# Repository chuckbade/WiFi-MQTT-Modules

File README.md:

Chuck Bade's Guide to using MQTT on ESP8266-Based Modules with JMRI for Model Trains

Update: All the sketches have been updated to be OTA-compatible (Over The Air programming). 
This will allow you to make updates without connecting the USB cable to the module.  The
first time you load one of these sketches however, you will have to use the cable and select the COM port, but after that you will be able to select the network port that's shown on the serial monitor on startup.  If you're using a WiFi connection on your PC, make sure the connection is set for Private not Public.

This is an inexpensive system of hardware and software for running model train accessories with JMRI.  I'm using a DCC++ setup for a base station, but any base station should be able to be used, as long as JMRI will allow the MQTT protocol to exist along side the other protocol.  Each module has a ESP8266-based Wemos D1 Mini (or compatible) that sends and receives messages to and from JMRI.  These messages are sent via the MQTT protocol, which makes programming very straightforward using the Arduino IDE.  JMRI is setup to use both the MQTT and DCC++ protocols.

Note this uses both the DCC++ connection from JMRI, and the MQTT connection.  Each module connects to the MQTT broker and uses specific topics and messages to communicate with JMRI.  Outputs are prefixed with MT and inputs are prefixed with MS.

To build a system, you will need some knowledge of electronics and software, but only at a hobbyist's level.  Before taking this on, I would recommend buying a D1 Mini and programming it to flash the on-board LED, then hook up an external LED and make it flash.  If you get that working, you've done the hard part, getting Arduino IDE set up.

I currently have 8 circuit boards designed for use with JMRI/MQTT.  
- BC Shield - Used for feed the DCC signal to block controllers using standard CAT5 cables.
- Block Controller - Tested and in use on my layout.
- Turnout Controller - Tested and in use on my layout.
- Turntable Controller - Nearly ready, still has a bug.
- 5 Ray Sensor - For 5 rays of a staging yard or turntable.
- Bridge Detector - For connecting two optical sensors under a turntable bridge.
- MQTT Monitor - A useful LCD-based monitoring tool that can send messages.
- Robocut - For running a servo inside a boxcar to uncouple other cars from it.
- 
I may sell blank boards or just provide the files to have your own made.  I haven't decided which way to go with that.

I am a retired software engineer, and I have been involved in electronics since my dad bought some CK722 transistors and a book from Berstein Applebee, from which we built various circuits. Now I design my own hardware and write the software to run it.  I was trained in electronics (PMEL) in the Marine Corps and since I never had a formal education in electrical engineering, my designs are based on what I've learned along the way and are a product of much trial and some error. I have a Bachelor's Degree in Computer Science.

I had tried to use S88N to monitor sensors around the layout, but found it to be prone to electrical noise, so S88 is gone, but I've repurposed the CAT5 cables to route the DCC signal and power to the block controllers.  There's too much voltage drop to maintain an adequate level from the five volt supply, so some extra voltage taps are required at the far ends of the the layout.  My train room is 15' by 15' with track on all four walls.

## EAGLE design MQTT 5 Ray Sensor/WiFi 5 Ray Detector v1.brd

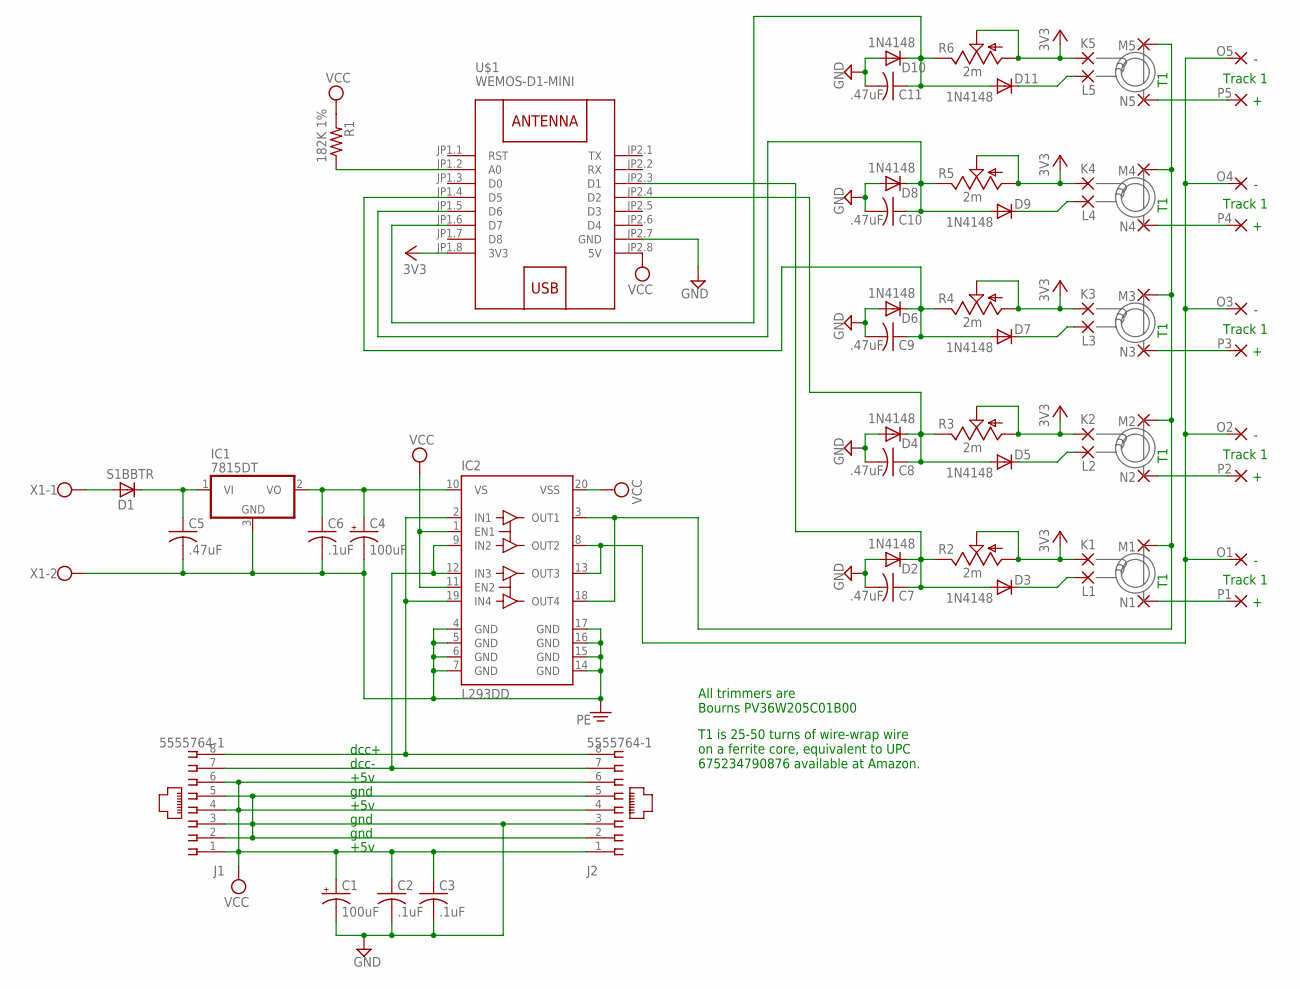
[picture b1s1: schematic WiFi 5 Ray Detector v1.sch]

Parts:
C1, C4: 100uF; E3,5-8
C2, C3, C6: .1uF; C1206
C5, C7, C8, C9, C10, C11: .47uF; C1206
D1: S1BBTR; DO-214AC
D2, D3, D4, D5, D6, D7, D8, D9, D10, D11: 1N4148; SOD123
IC1: 7815DT; TO252
IC2: L293DD; SO20
J1, J2: 5555764-1; 520426-4
K1, K2, K3, K4, K5: 2,15/1,0
L1, L2, L3, L4, L5: 2,15/1,0
M1, M2, M3, M4, M5: NA; 2,15/1,0
N1, N2, N3, N4, N5: NA; 2,15/1,0
O1, O2, O3, O4, O5: NA; 2,15/1,0
P1, P2, P3, P4, P5: NA; 2,15/1,0
R1: 182K 1%; M1206
R2, R3, R4, R5, R6: 2m; S63P
U$1: WEMOS-D1-MINI
X1: W237-102

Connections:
3V3: K1.1, K2.1, K3.1, K4.1, K5.1, R2.A, R2.S, R3.A, R3.S, R4.A, R4.S, R5.A, R5.S, R6.A, R6.S, U$1.JP1.8 (3V3)
GND: C1.-, C2.2, C3.2, C7.2, C8.2, C9.2, C10.2, C11.2, D2.A, D4.A, D6.A, D8.A, D10.A, J1.2, J1.3, J1.5, J2.2, J2.3, J2.5, U$1.JP2.7 (GND)
J1: N1.1, P1.1
J2: N2.1, P2.1
J3: N3.1, P3.1
J4: N4.1, P4.1
J5: N5.1, P5.1
unnamed: D5.C, L2.1
unnamed: C9.1, D6.C, D7.A, R4.E, U$1.JP1.4 (D5)
unnamed: C7.1, D2.C, D3.A, R2.E, U$1.JP2.3 (D1)
unnamed: D1.A, X1.1
unnamed: C5.1, D1.C, IC1.1 (VI)
unnamed: C8.1, D4.C, D5.A, R3.E, U$1.JP2.4 (D2)
unnamed: IC2.9 (IN2), IC2.12 (IN3), J1.7, J2.7
unnamed: D7.C, L3.1
unnamed: C10.1, D8.C, D9.A, R5.E, U$1.JP1.5 (D6)
unnamed: D9.C, L4.1
unnamed: C11.1, D10.C, D11.A, R6.E, U$1.JP1.6 (D7)
unnamed: R1.1, U$1.JP1.2 (A0)
unnamed: D11.C, L5.1
unnamed: IC2.2 (IN1), IC2.19 (IN4), J1.8, J2.8
unnamed: D3.C, L1.1
OUT+: IC2.3 (OUT1), IC2.18 (OUT4), M1.1, M2.1, M3.1, M4.1, M5.1
OUT-: IC2.8 (OUT2), IC2.13 (OUT3), O1.1, O2.1, O3.1, O4.1, O5.1
PE: C4.-, C5.2, C6.2, IC1.3 (GND), IC2.4 (GND), IC2.5 (GND), IC2.6 (GND), IC2.7 (GND), IC2.14 (GND), IC2.15 (GND), IC2.16 (GND), IC2.17 (GND), X1.2
VCC: C1.+, C2.1, C3.1, IC2.1 (EN1), IC2.11 (EN2), IC2.20 (VSS), J1.1, J1.4, J1.6, J2.1, J2.4, J2.6, R1.2, U$1.JP2.8 (5V)
VS: C4.+, C6.1, IC1.2 (VO), IC2.10 (VS)

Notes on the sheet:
gnd
+5v
dcc+
dcc-
T1 is 25-50 turns of wire-wrap wire on a ferrite core, equivalent to UPC 675234790876 available at Amazon.
All trimmers are Bourns‎ PV36W205C01B00
Track 1

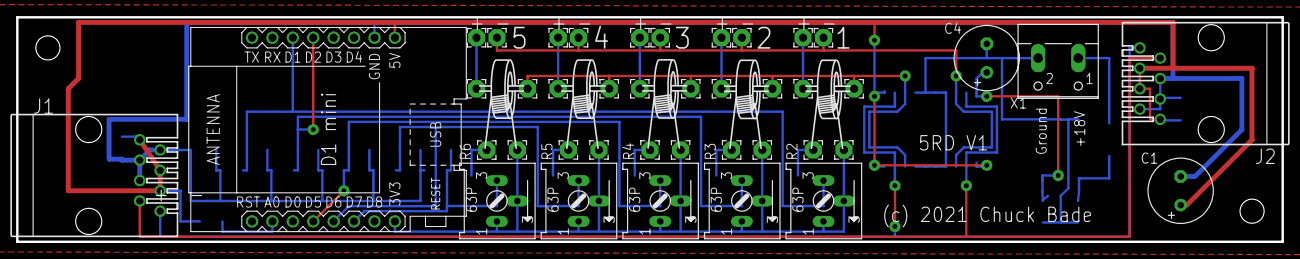
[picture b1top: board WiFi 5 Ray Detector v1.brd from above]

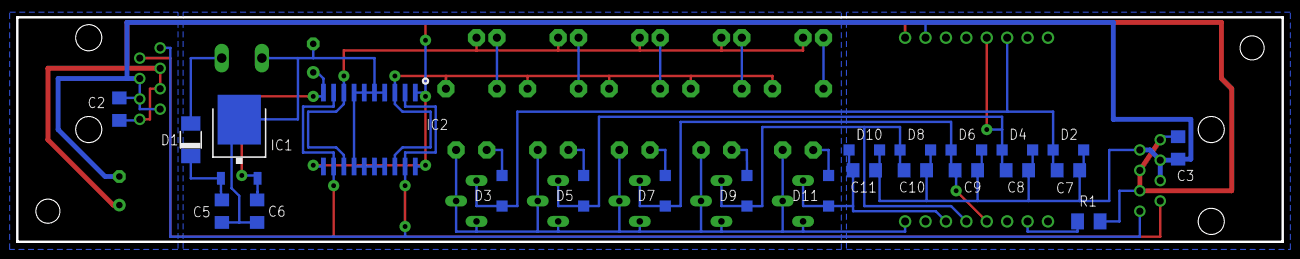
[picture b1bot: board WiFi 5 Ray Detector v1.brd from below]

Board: 2 copper layers, 157.5 x 27.9 mm, 66 parts (23 on the bottom side), 27 nets.

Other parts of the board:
U$3, U$4: 4-40SCREW

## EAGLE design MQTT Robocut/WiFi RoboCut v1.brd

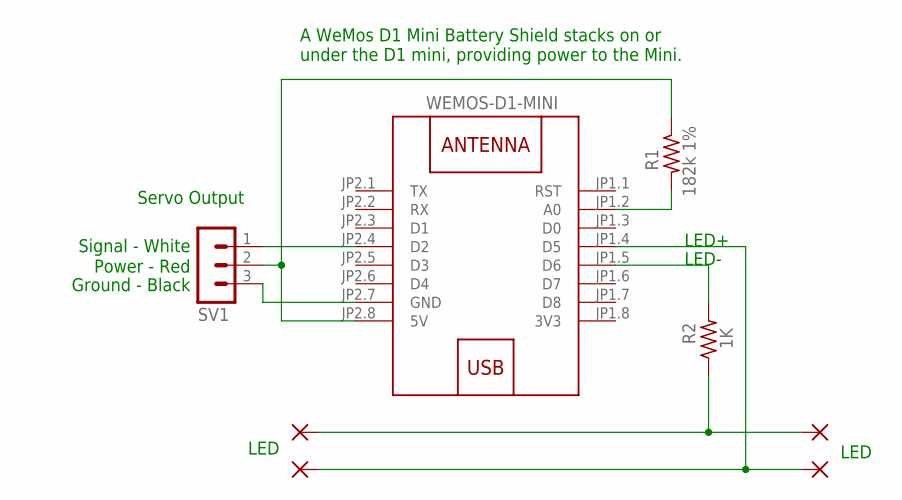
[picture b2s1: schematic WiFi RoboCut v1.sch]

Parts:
PAD1, PAD2, PAD3, PAD4: 2,15/1,0
R1: 182k 1%; R1206
R2: 1K; R1206
SV1: MA03-1
U$1: WEMOS-D1-MINI

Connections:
3V3: U$1.JP1.8 (3V3)
GND: SV1.3, U$1.JP2.7 (GND)
unnamed: R1.2, U$1.JP1.2 (A0)
unnamed: SV1.1, U$1.JP2.4 (D2)
unnamed: PAD1.1, PAD3.1, R2.1
unnamed: PAD2.1, PAD4.1, U$1.JP1.4 (D5)
unnamed: R2.2, U$1.JP1.5 (D6)
VCC: R1.1, SV1.2, U$1.JP2.8 (5V)

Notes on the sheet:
LED+
LED-
Signal - White
Power - Red
Ground - Black
Servo Output
LED
A WeMos D1 Mini Battery Shield stacks on or under the D1 mini, providing power to the Mini.

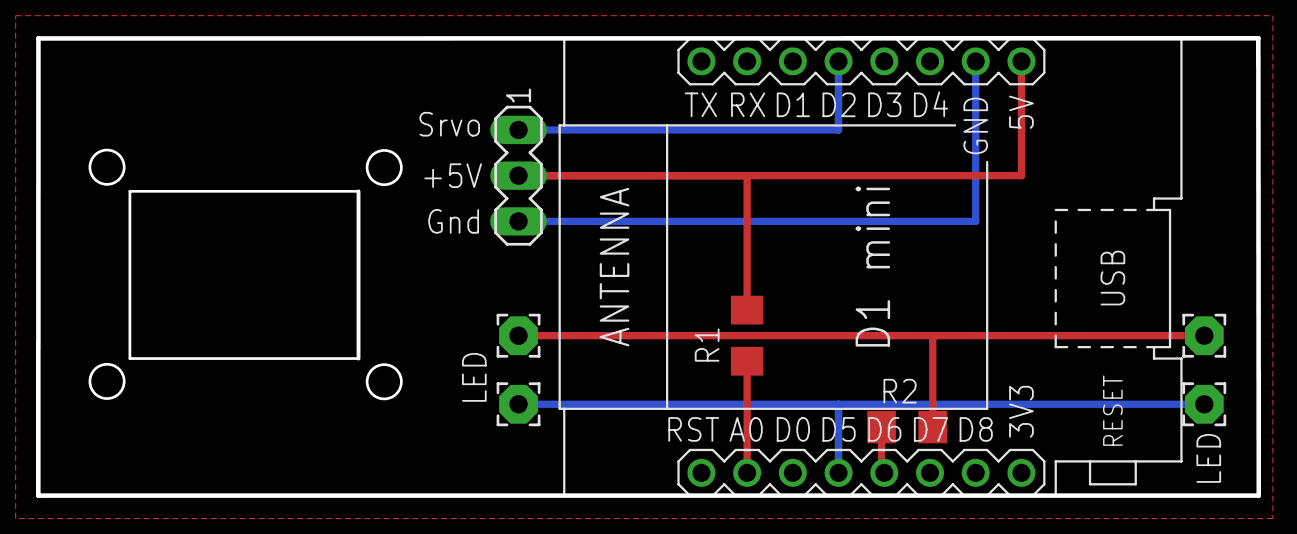
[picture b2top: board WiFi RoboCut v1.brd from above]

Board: 2 copper layers, 67.8 x 25.4 mm, 8 parts (0 on the bottom side), 7 nets.

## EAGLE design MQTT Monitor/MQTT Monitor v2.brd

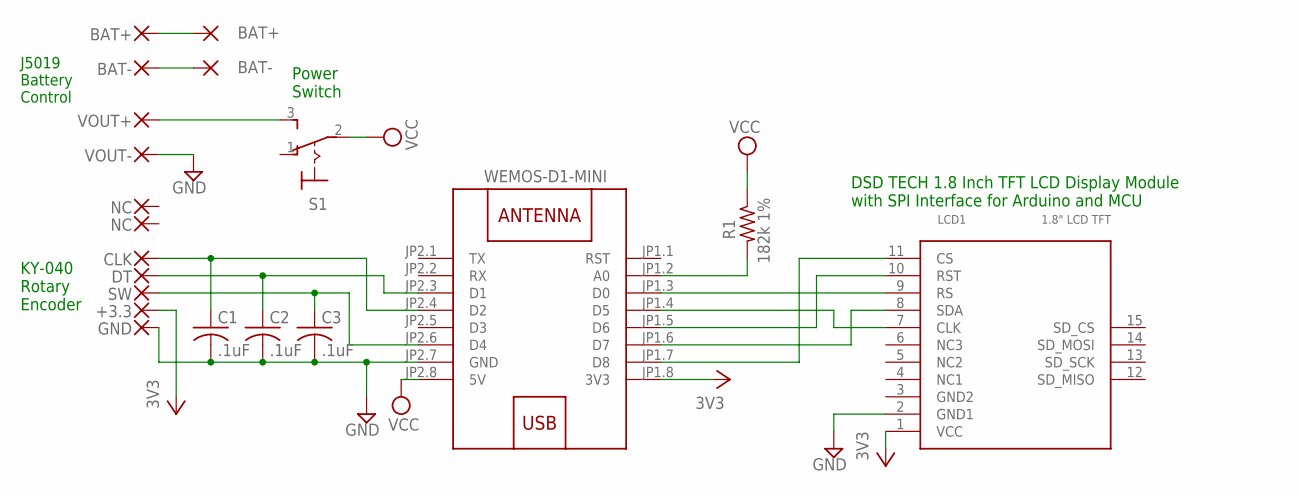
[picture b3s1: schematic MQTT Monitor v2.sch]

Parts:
C1, C2, C3: .1uF; C1206
LCD1: 1.8" LCD TFT; DSDTECH1.8"TFT
PAD1: CLK; 2,15/1,0
PAD2: DT; 2,15/1,0
PAD3: SW; 2,15/1,0
PAD4: +3.3; 2,15/1,0
PAD5: GND; 2,15/1,0
PAD6: VOUT+; 2,15/1,0
PAD7: VOUT-; 2,15/1,0
PAD8, PAD10: BAT+; 2,15/1,0
PAD9, PAD11: BAT-; 2,15/1,0
PAD12, PAD13: NC; 2,15/1,0
R1: 182k 1%; R1206
S1: 320-916
U$1: WEMOS-D1-MINI

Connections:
3V3: LCD1.1 (VCC), PAD4.1, U$1.JP1.8 (3V3)
5V: R1.1, S1.2, U$1.JP2.8 (5V)
GND: C1.2, C2.2, C3.2, LCD1.2 (GND1), PAD5.1, PAD7.1, U$1.JP2.7 (GND)
unnamed: R1.2, U$1.JP1.2 (A0)
unnamed: C3.1, PAD3.1, U$1.JP2.6 (D4)
unnamed: LCD1.7 (CLK), U$1.JP1.4 (D5)
unnamed: LCD1.8 (SDA), U$1.JP1.6 (D7)
unnamed: LCD1.9 (RS), U$1.JP1.3 (D0)
unnamed: LCD1.10 (RST), U$1.JP1.5 (D6)
unnamed: LCD1.11 (CS), U$1.JP1.7 (D8)
unnamed: PAD8.1, PAD10.1
unnamed: PAD9.1, PAD11.1
unnamed: C2.1, PAD2.1, U$1.JP2.3 (D1)
unnamed: C1.1, PAD1.1, U$1.JP2.4 (D2)
unnamed: PAD6.1, S1.3 (S)

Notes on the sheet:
KY-040 Rotary Encoder
J5019 Battery Control
Power Switch
DSD TECH 1.8 Inch TFT LCD Display Module with SPI Interface for Arduino and MCU

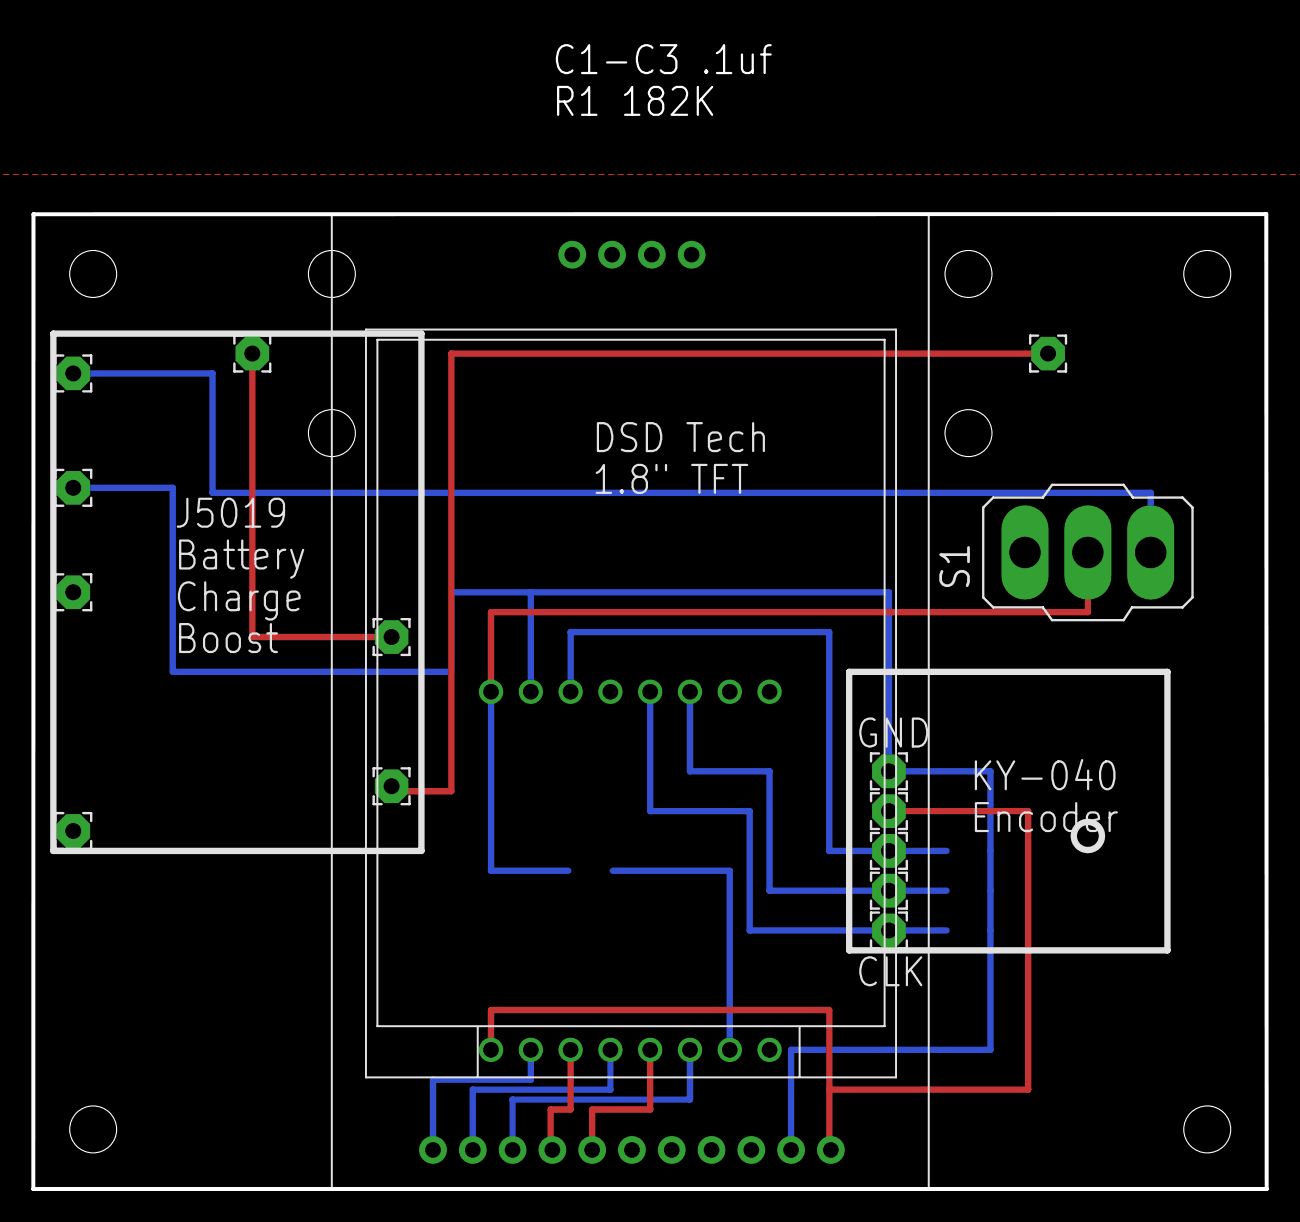
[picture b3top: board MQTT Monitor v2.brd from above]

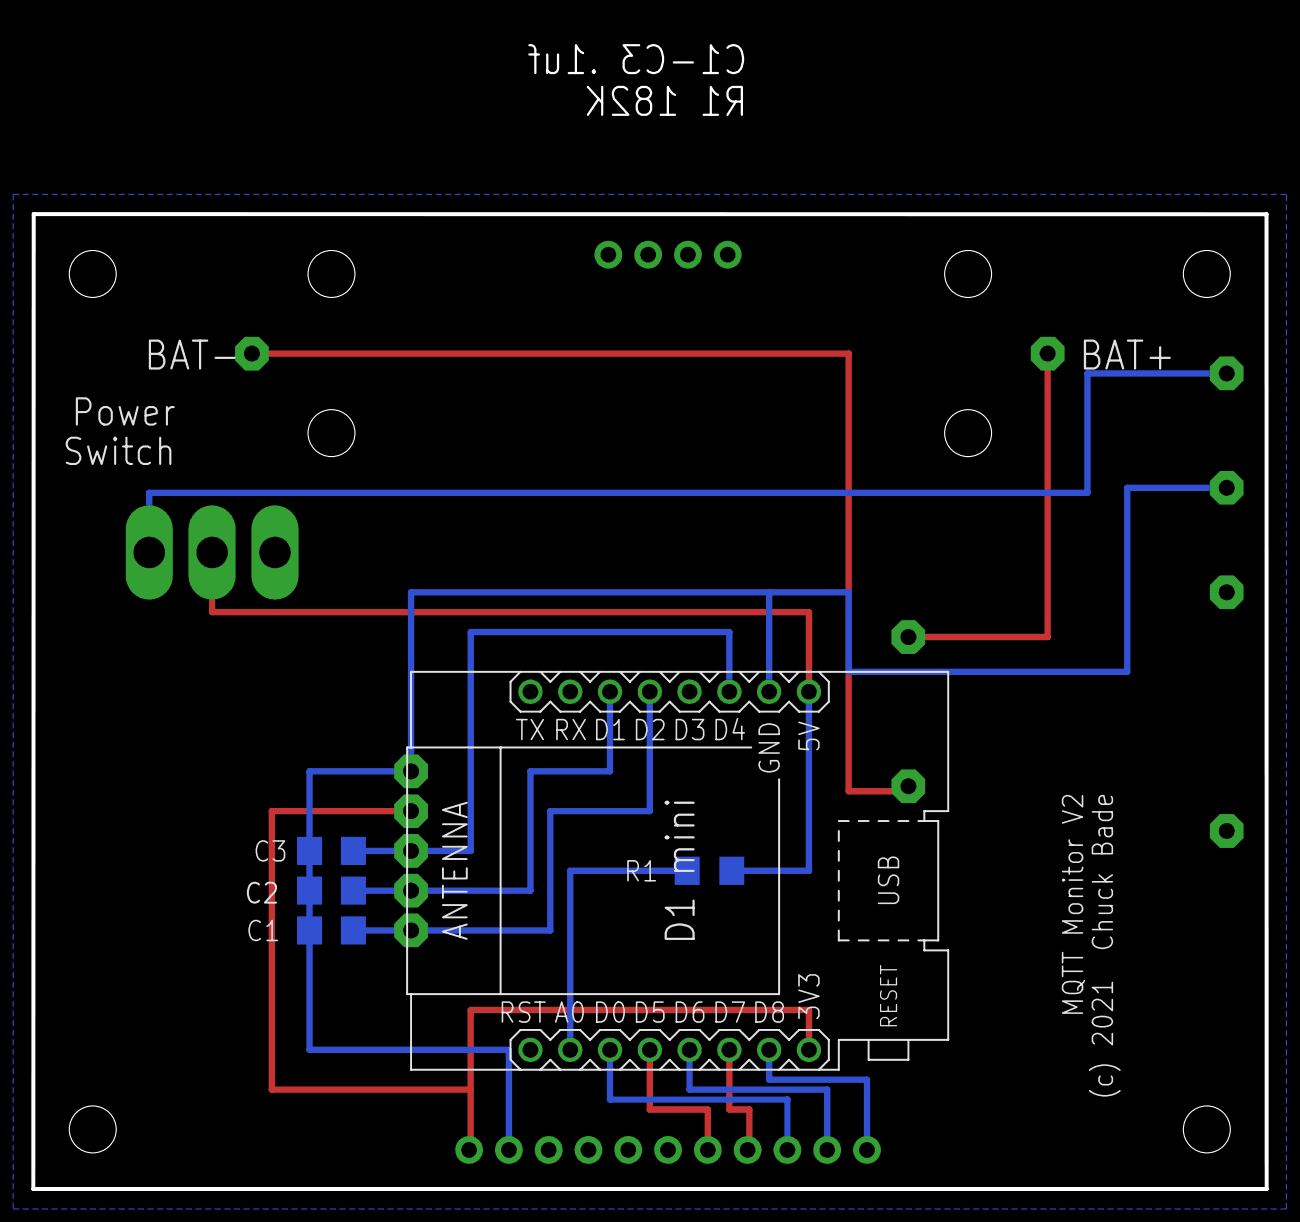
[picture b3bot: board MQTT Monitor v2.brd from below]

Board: 2 copper layers, 78.7 x 73.8 mm, 28 parts (13 on the bottom side), 15 nets.

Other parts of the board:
U$3, U$4, U$5, U$6, U$7, U$8, U$9, U$10: 4-40SCREW

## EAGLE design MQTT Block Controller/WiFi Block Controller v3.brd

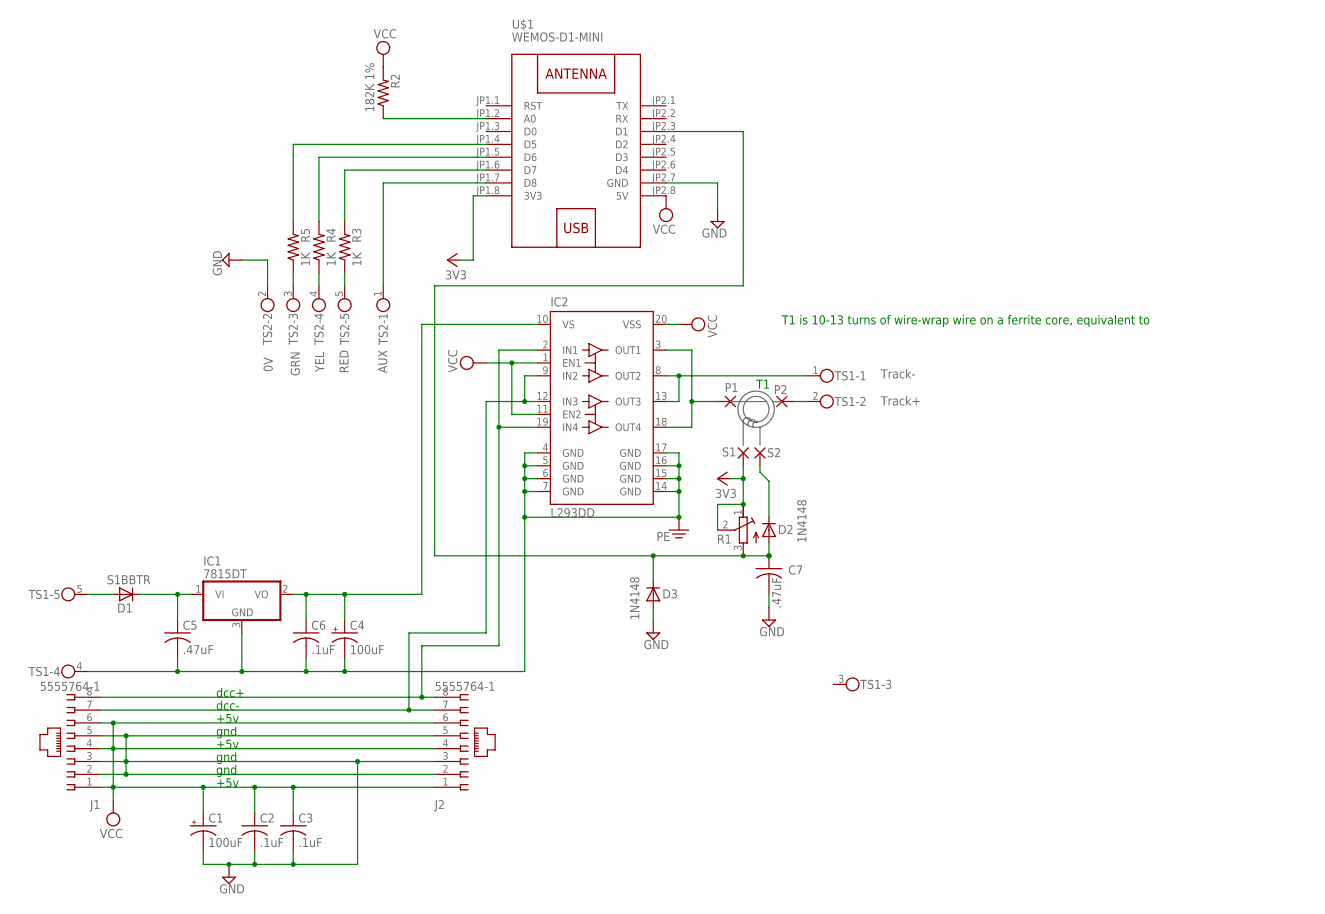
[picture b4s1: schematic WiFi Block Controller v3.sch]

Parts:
C1, C4: 100uF; E3,5-8
C2, C3, C6: .1uF; C1206
C5, C7: .47uF; C1206
D1: S1BBTR; DO-214AC
D2, D3: 1N4148; SOD123
IC1: 7815DT; TO252
IC2: L293DD; SO20
J1, J2: 5555764-1; 520426-4
P1, P2: NA; 2,15/1,0
R1: R-TRIMM3314G; RTRIM3314G
R2: 182K 1%; M1206
R3, R4, R5: 1K; M1206
S1, S2: 2,15/1,0
TS1, TS2: TERMBLK05; 05PB
U$1: WEMOS-D1-MINI

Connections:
3V3: R1.1 (E), R1.2 (S), S1.1, U$1.JP1.8 (3V3)
GND: C1.-, C2.2, C3.2, C7.2, D3.A, J1.2, J1.3, J1.5, J2.2, J2.3, J2.5, TS2.2, U$1.JP2.7 (GND)
unnamed: R5.1, TS2.3
unnamed: R3.1, TS2.5
unnamed: C7.1, D2.A, D3.C, R1.3 (A), U$1.JP2.3 (D1)
unnamed: D1.A, TS1.5
unnamed: C5.1, D1.C, IC1.1 (VI)
unnamed: IC2.9 (IN2), IC2.12 (IN3), J1.7, J2.7
unnamed: R4.1, TS2.4
unnamed: R2.1, U$1.JP1.2 (A0)
unnamed: R5.2, U$1.JP1.4 (D5)
unnamed: R4.2, U$1.JP1.5 (D6)
unnamed: R3.2, U$1.JP1.6 (D7)
unnamed: IC2.2 (IN1), IC2.19 (IN4), J1.8, J2.8
unnamed: TS2.1, U$1.JP1.7 (D8)
unnamed: P2.1, TS1.2
unnamed: IC2.3 (OUT1), IC2.18 (OUT4), P1.1
unnamed: IC2.8 (OUT2), IC2.13 (OUT3), TS1.1
unnamed: D2.C, S2.1
PE: C4.-, C5.2, C6.2, IC1.3 (GND), IC2.4 (GND), IC2.5 (GND), IC2.6 (GND), IC2.7 (GND), IC2.14 (GND), IC2.15 (GND), IC2.16 (GND), IC2.17 (GND), TS1.4
VCC: C1.+, C2.1, C3.1, IC2.1 (EN1), IC2.11 (EN2), IC2.20 (VSS), J1.1, J1.4, J1.6, J2.1, J2.4, J2.6, R2.2, U$1.JP2.8 (5V)
VS: C4.+, C6.1, IC1.2 (VO), IC2.10 (VS)

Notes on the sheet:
gnd
+5v
dcc+
Track+
Track-
GRN
YEL
RED
AUX
dcc-
T1 is 10-13 turns of wire-wrap wire on a ferrite core, equivalent to

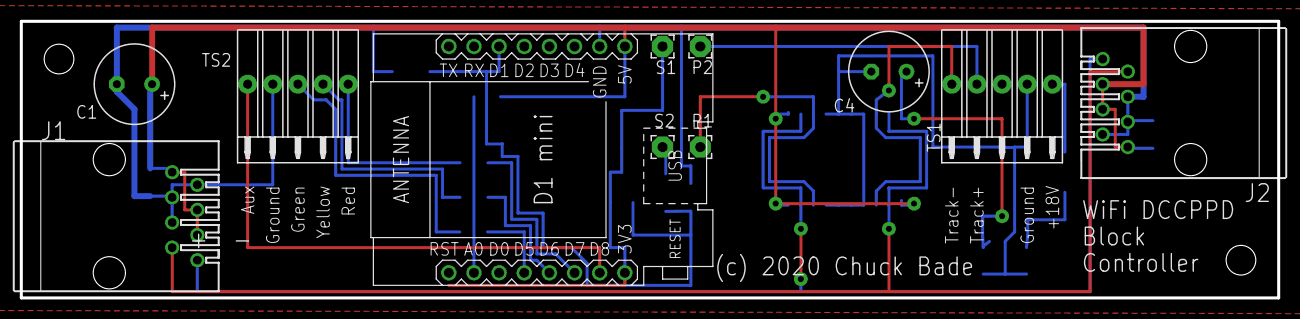
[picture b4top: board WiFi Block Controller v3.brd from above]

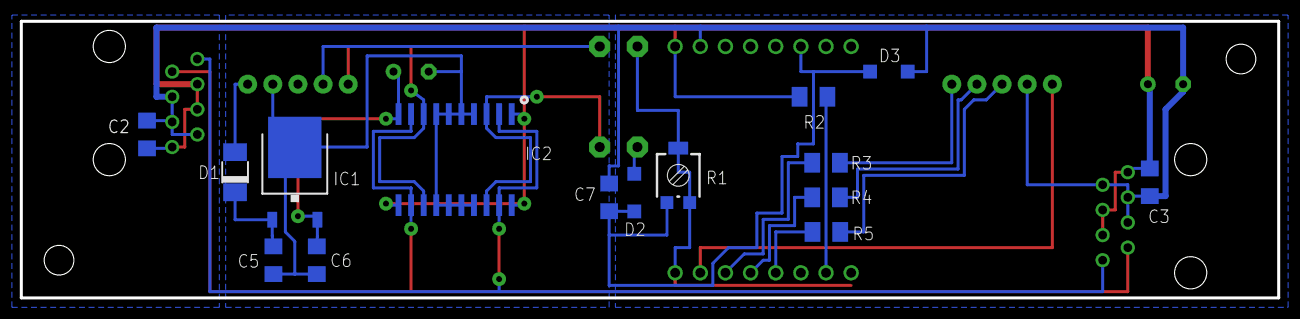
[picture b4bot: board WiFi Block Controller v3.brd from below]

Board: 2 copper layers, 127.0 x 27.9 mm, 28 parts (15 on the bottom side), 22 nets.

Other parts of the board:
U$3, U$4: 4-40SCREW

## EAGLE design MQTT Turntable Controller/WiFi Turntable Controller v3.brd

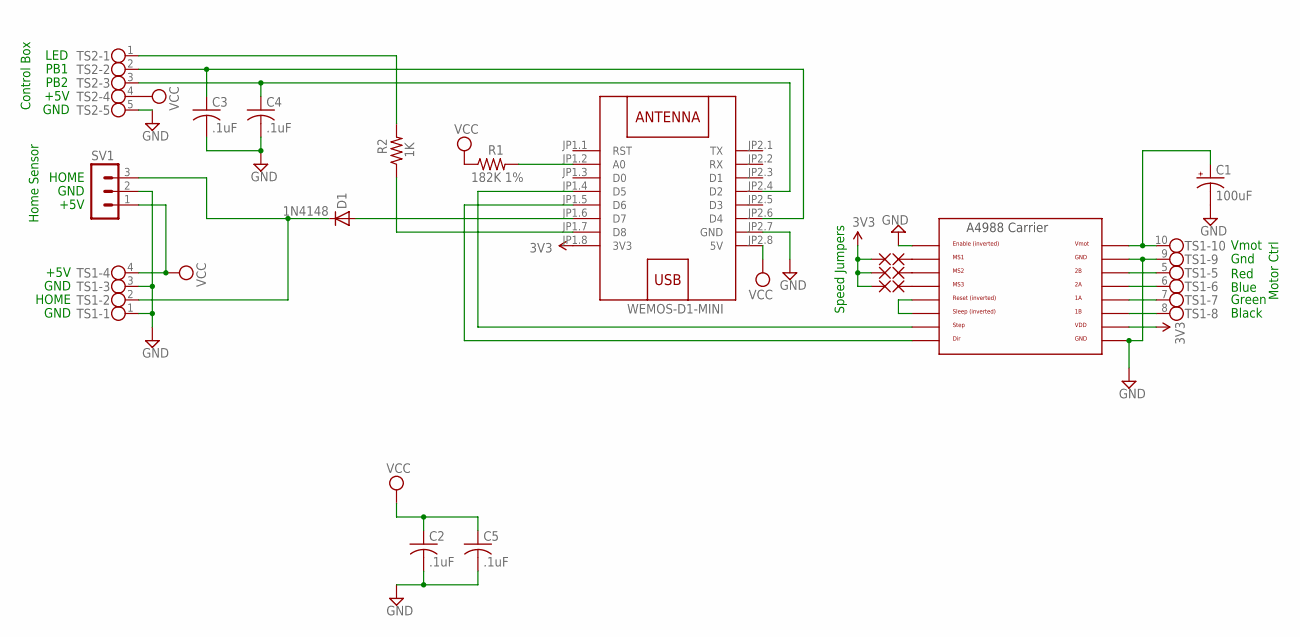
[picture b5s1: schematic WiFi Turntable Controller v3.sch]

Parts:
C1: 100uF; E3,5-8
C2, C3, C4, C5: .1uF; C1206
D1: 1N4148; SOD123
PAD1, PAD2, PAD3, PAD4, PAD5, PAD6: 1,6/0,8
R1: 182K 1%; R1206
R2: 1K; R1206
SV1: MA03-1
TS1: TERMBLK10; 10PB
TS2: TERMBLK05; 05PB
U$1: WEMOS-D1-MINI
U$2: A4988BREAKOUT

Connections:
3.3V: PAD4.1, PAD5.1, PAD6.1, U$1.JP1.8 (3V3), U$2.VDD
GND: C1.-, C2.2, C3.2, C4.2, C5.2, SV1.2, TS1.1, TS1.3, TS1.9, TS2.5, U$1.JP2.7 (GND), U$2.EN, U$2.GND, U$2.GND@0 (GND)
unnamed: D1.A, U$1.JP1.6 (D7)
unnamed: D1.C, SV1.3, TS1.2
unnamed: U$2.RST, U$2.SLP (SLEEP)
unnamed: U$1.JP1.4 (D5), U$2.STEP
unnamed: PAD1.1, U$2.MS1
unnamed: PAD2.1, U$2.MS2
unnamed: R1.2, U$1.JP1.2 (A0)
unnamed: U$1.JP1.5 (D6), U$2.DIR
unnamed: PAD3.1, U$2.MS3
unnamed: TS1.5, U$2.2B
unnamed: TS1.6, U$2.2A
unnamed: TS1.7, U$2.1A
unnamed: TS1.8, U$2.1B
unnamed: R2.2, TS2.1
unnamed: C3.1, TS2.2, U$1.JP2.6 (D4)
unnamed: C4.1, TS2.3, U$1.JP2.4 (D2)
unnamed: R2.1, U$1.JP1.7 (D8)
VCC: C2.1, C5.1, R1.1, SV1.1, TS1.4, TS2.4, U$1.JP2.8 (5V)
VMOT: C1.+, TS1.10, U$2.VMOT

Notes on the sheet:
+5V
GND
HOME
Home Sensor
LED
PB1
PB2
Red
Blue
Green
Black
Vmot
Gnd
Control Box
Speed Jumpers
Motor Ctrl

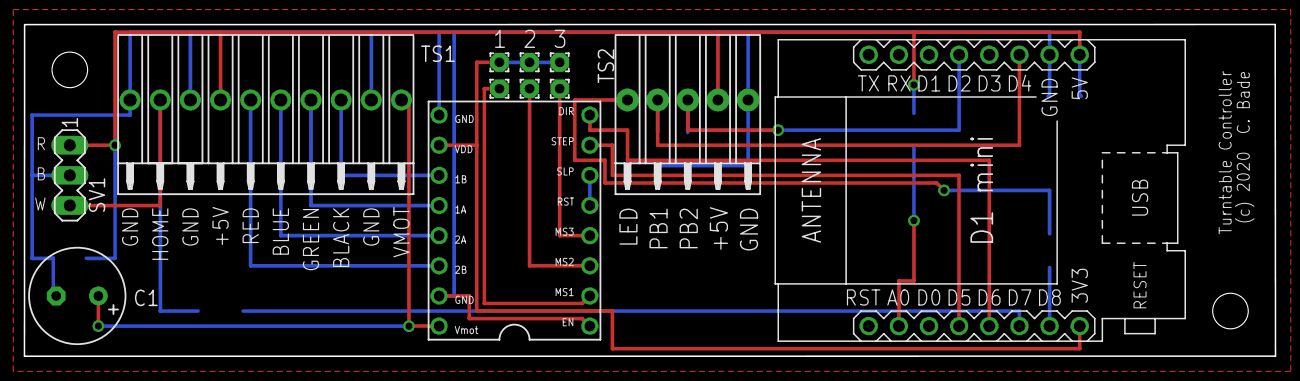
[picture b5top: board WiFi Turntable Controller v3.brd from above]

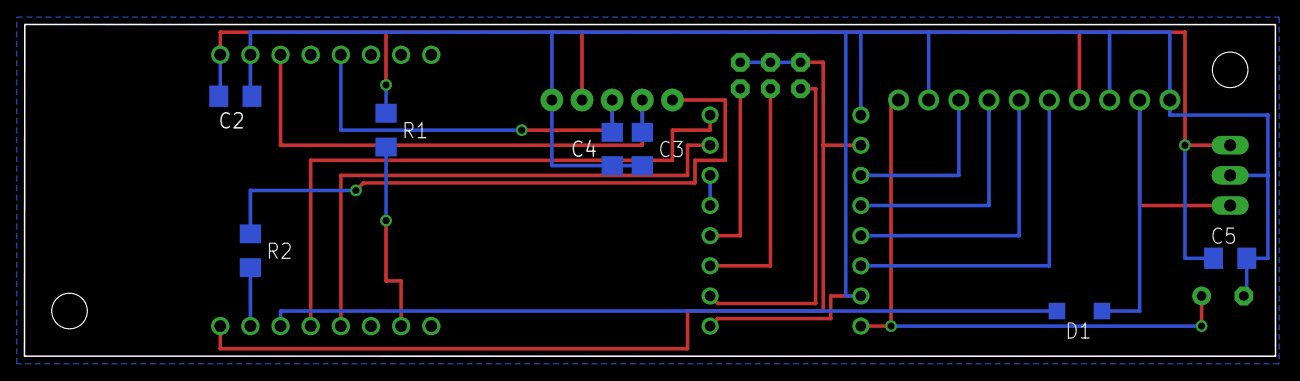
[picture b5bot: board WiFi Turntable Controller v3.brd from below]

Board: 2 copper layers, 105.4 x 27.9 mm, 21 parts (9 on the bottom side), 21 nets.

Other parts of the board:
U$3, U$4: 4-40SCREW

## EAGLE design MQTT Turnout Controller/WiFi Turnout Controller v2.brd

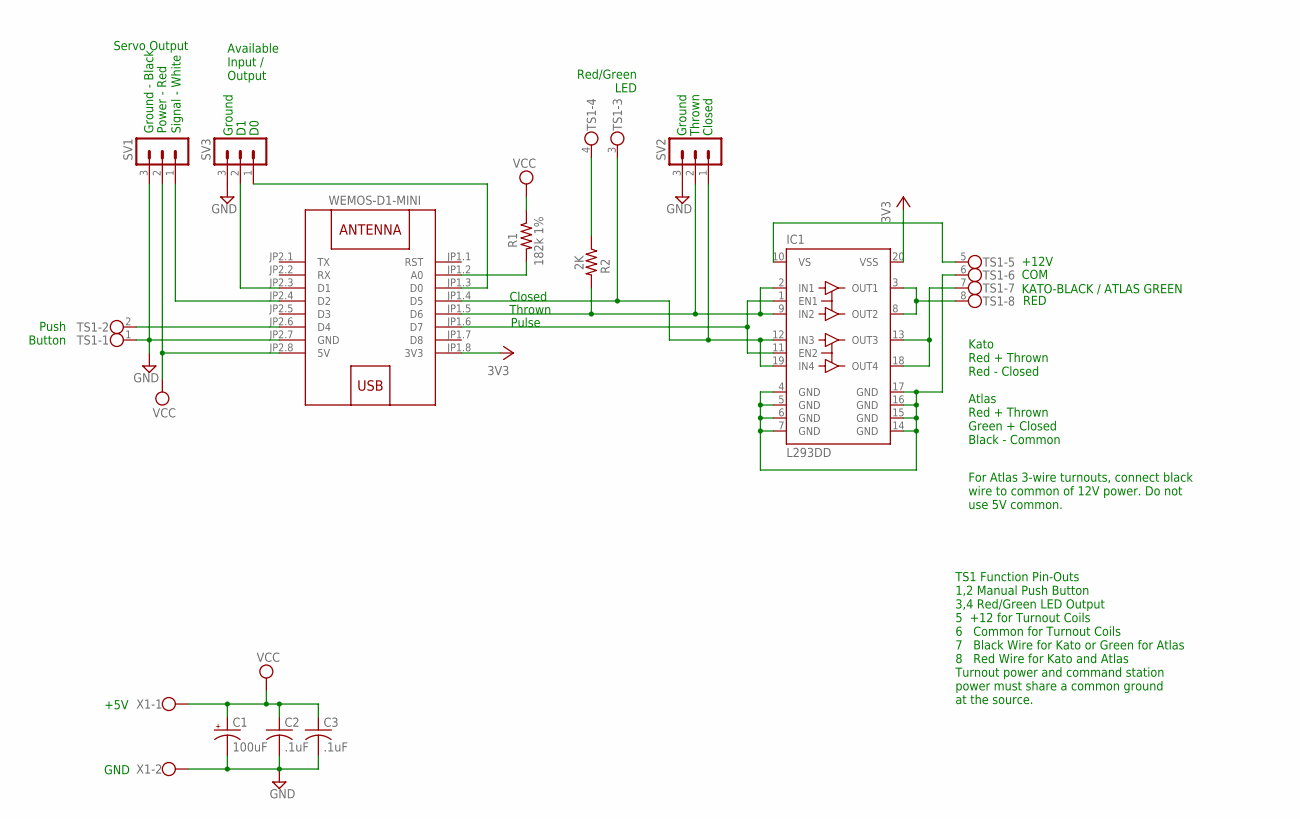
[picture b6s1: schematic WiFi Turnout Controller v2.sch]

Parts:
C1: 100uF; E3,5-8
C2, C3: .1uF; C1206
IC1: L293DD; SO20
R1: 182k 1%; R1206
R2: 2K; R1206
SV1, SV2, SV3: MA03-1
TS1: TERMBLK08; 08PB
U$1: WEMOS-D1-MINI
X1: W237-102

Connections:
3V3: IC1.20 (VSS), U$1.JP1.8 (3V3)
COM: IC1.4 (GND), IC1.5 (GND), IC1.6 (GND), IC1.7 (GND), IC1.14 (GND), IC1.15 (GND), IC1.16 (GND), IC1.17 (GND), TS1.6
GND: C1.-, C2.2, C3.2, SV1.3, SV2.3, SV3.3, TS1.1, U$1.JP2.7 (GND), X1.2
unnamed: R1.2, U$1.JP1.2 (A0)
unnamed: SV1.1, U$1.JP2.4 (D2)
unnamed: SV3.1, U$1.JP1.3 (D0)
unnamed: TS1.2, U$1.JP2.6 (D4)
unnamed: SV3.2, U$1.JP2.3 (D1)
unnamed: R2.1, TS1.4
unnamed: IC1.12 (IN3), IC1.19 (IN4), SV2.1, TS1.3, U$1.JP1.4 (D5)
unnamed: IC1.2 (IN1), IC1.9 (IN2), R2.2, SV2.2, U$1.JP1.5 (D6)
unnamed: IC1.1 (EN1), IC1.11 (EN2), U$1.JP1.6 (D7)
unnamed: IC1.13 (OUT3), IC1.18 (OUT4), TS1.7
unnamed: IC1.3 (OUT1), IC1.8 (OUT2), TS1.8
VCC: C1.+, C2.1, C3.1, R1.1, SV1.2, U$1.JP2.8 (5V), X1.1
VS: IC1.10 (VS), TS1.5

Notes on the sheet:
Push Button
Kato Red + Thrown Red - Closed Atlas Red + Thrown Green + Closed Black - Common
+12V
COM
RED
KATO-BLACK / ATLAS GREEN
For Atlas 3-wire turnouts, connect black wire to common of 12V power. Do not use 5V common.
TS1 Function Pin-Outs 1,2 Manual Push Button 3,4 Red/Green LED Output 5 +12 for Turnout Coils 6 Common for Turnout Coils 7 Black Wire for Kato or Green for Atlas 8 Red Wire for Kato and Atlas Turnout power and command station power must share a common ground at the source.
Closed
Red/Green LED
Pulse
Thrown
Signal - White
Power - Red
Ground - Black
Servo Output
Ground
+5V
GND
Available Input / Output

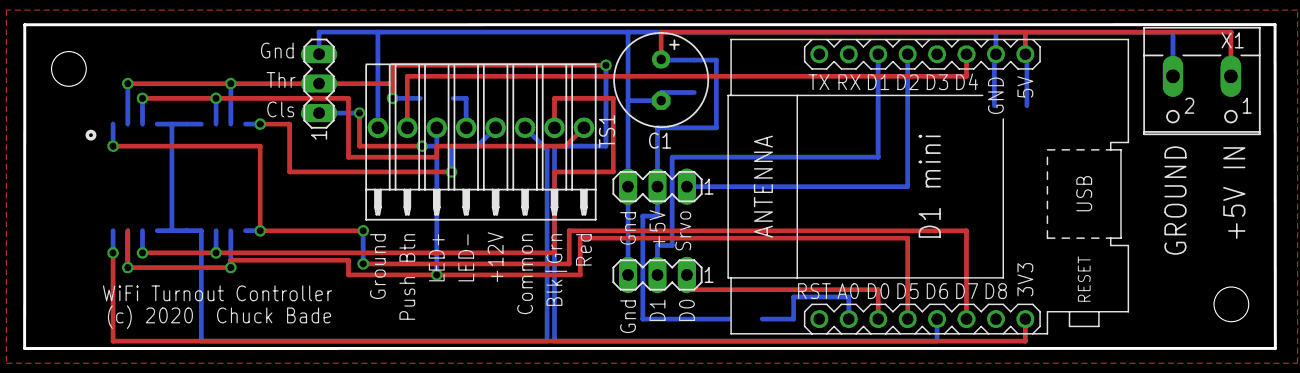
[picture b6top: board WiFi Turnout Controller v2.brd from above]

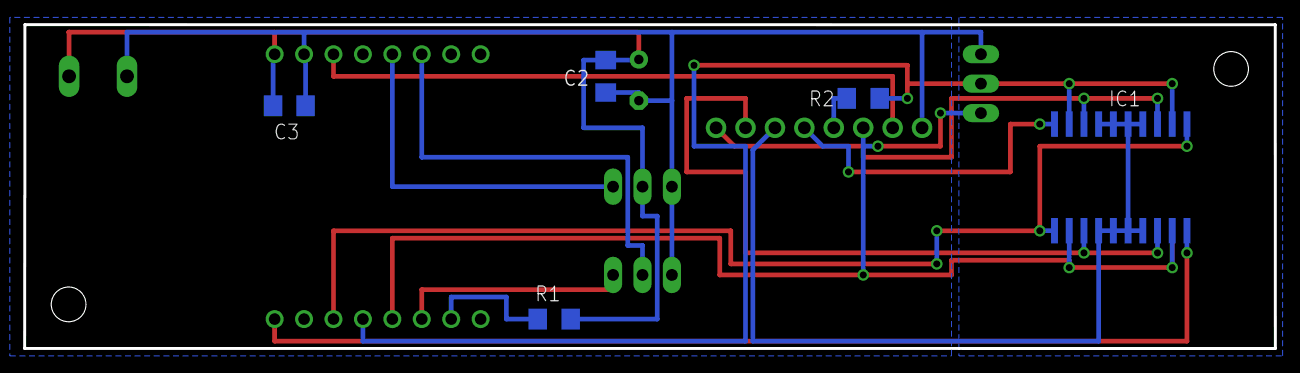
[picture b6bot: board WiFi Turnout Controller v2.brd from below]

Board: 2 copper layers, 107.9 x 27.9 mm, 14 parts (7 on the bottom side), 16 nets.

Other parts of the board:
U$3, U$4: 4-40SCREW

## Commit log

2020-10-14 Wifi MQTT Module release
    This new repository removes references to DCC++, as it is no longer required for my modules to communicate with JMRI.
2020-10-15 added eagle files
2020-10-26 Update with new home sensor
2020-10-26 removed old versions
2020-11-08 Update mqtt_turnout_d1_v2.0.ino
    Fixed IP address display and removed eeprom addr display
2020-11-09 For Rob
    Added a 2 sensor sketch for Rob.
2020-11-11 updated with toString on ip
    Also made extensive changes to turnout controller, to fix jerking on startup and corrected eeprom startup
2020-11-23 Update to v3 board
    I ordered them under v2 but needed new file names to release.
2020-11-25 Update with small change
    Moved MQTT server IP definition to header file in sketches that didn't have it yet.
2020-11-26 Created PDFs
    Replaced the odt files with PDFs
2021-01-25 Added MQTT Monitor
    Also update bridge detector
2021-01-25 Added Robocut
2021-02-22 Create mqtt_5_sensor_d1_v1.ino
    New file.
2021-02-23 Update and add files
2021-03-01 Update MQTT 5 Ray Sensor Instructions.pdf
    Improved Figure 1 to better show diode polarity
2021-03-01 Update MQTT 5 Ray Sensor Instructions.pdf
    oops
2021-03-20 Update
    Improved analog reporting by adding smoothing feature.
2021-03-20 Update MQTT Instructions.pdf
    Added a few lines.
2021-03-20 Added analog averaging
2021-03-21 Update mqtt_robocut_d1_v1.ino
    Added analog averaging
2021-03-24 Removed analog feature.
2021-03-25 Udates to several files.
    Primarily eliminating analog reading feature.
2021-04-01 Removed analog reporting.
2021-04-15 Update mqtt_turntable_d1_v1.1.ino
    I think I fixed the startup homing error bug.
2021-04-19 Fixed (for real this time) startup bug
2021-04-23 Removed circuit board files.
    Updated README
2021-05-23 Removed TT Controller, not ready
2021-09-09 Added OTA capability to all.

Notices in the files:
MQTT 5 Ray Sensor/WiFi 5 Ray Detector v1.brd:
(c) 2021 Chuck Bade
MQTT Block Controller/WiFi Block Controller v3.brd:
(c) 2020 Chuck Bade
MQTT Turntable Controller/WiFi Turntable Controller v3.brd:
(c) 2020  C. Bade
parts and their libraries:
diy-modules: Released under the Creative Commons Attribution 4.0 International License: http://creativecommons.org/licenses/by/4.0
SparkFun: Licensing: CC v3.0 Share-Alike You are welcome to use this library for commercial purposes.
